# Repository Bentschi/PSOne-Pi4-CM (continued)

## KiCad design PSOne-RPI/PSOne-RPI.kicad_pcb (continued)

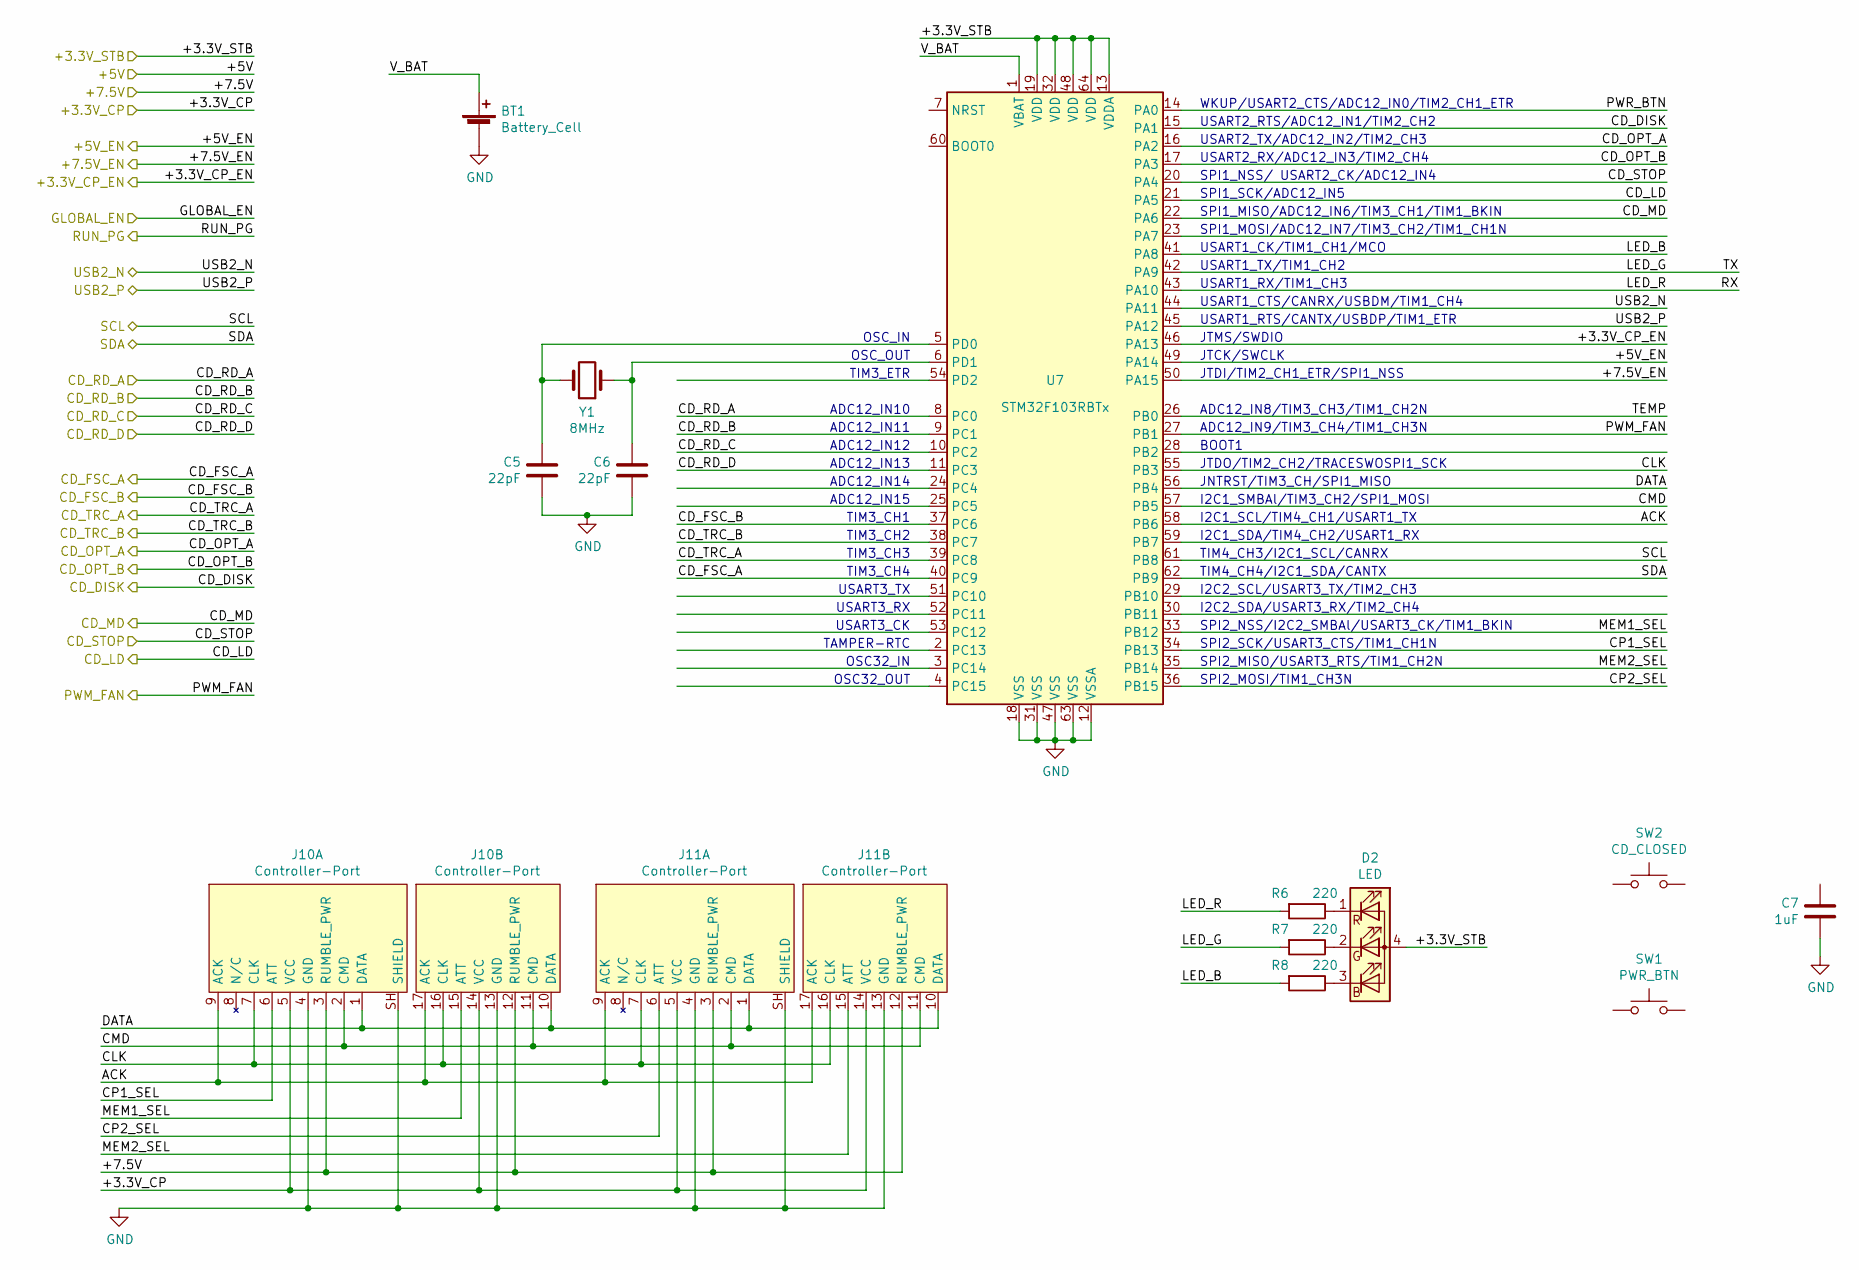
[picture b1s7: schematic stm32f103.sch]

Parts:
BT1: Battery_Cell; BatteryHolder_Keystone_1058_1x2032
C5, C6: 22pF; C_1206_3216Metric
C7: 1uF; C_1206_3216Metric
D2: LED; LED_RGB_1210
J10, J11: Controller-Port; PSOne-Controller-Port
R6, R7, R8: 220; R_1206_3216Metric
SW1: PWR_BTN; SW_Cherry_MX_1.00u_PCB
SW2: CD_CLOSED; SW_PUSH_6mm_H8.5mm
U7: STM32F103RBTx; LQFP-64_10x10mm_P0.5mm
Y1: 8MHz; Crystal_SMD_7050-2Pin_7.0x5.0mm

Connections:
/+3.3V_STB: D2.4 (A), U7.13 (VDDA), U7.19 (VDD), U7.32 (VDD), U7.48 (VDD), U7.64 (VDD); also elsewhere on the board
/+5V_EN: U7.49 (PA14)
/+7.5V: J10.3 (RUMBLE_PWR), J10.12 (RUMBLE_PWR), J11.3 (RUMBLE_PWR), J11.12 (RUMBLE_PWR); also elsewhere on the board
/+7.5V_EN: U7.50 (PA15)
/CD-Interface/+3.3V_CP: J10.5 (VCC), J10.14 (VCC), J11.5 (VCC), J11.14 (VCC); also elsewhere on the board
/CD-Interface/+3.3V_CP_EN: U7.46 (PA13)
/CD-Interface/CD_DISK: U7.15 (PA1); also elsewhere on the board
/CD-Interface/CD_FSC_A: U7.40 (PC9); also elsewhere on the board
/CD-Interface/CD_FSC_B: U7.37 (PC6); also elsewhere on the board
/CD-Interface/CD_LD: U7.21 (PA5); also elsewhere on the board
/CD-Interface/CD_MD: U7.22 (PA6); also elsewhere on the board
/CD-Interface/CD_OPT_A: U7.16 (PA2); also elsewhere on the board
/CD-Interface/CD_OPT_B: U7.17 (PA3); also elsewhere on the board
/CD-Interface/CD_RD_A: U7.8 (PC0); also elsewhere on the board
/CD-Interface/CD_RD_B: U7.9 (PC1); also elsewhere on the board
/CD-Interface/CD_RD_C: U7.10 (PC2); also elsewhere on the board
/CD-Interface/CD_RD_D: U7.11 (PC3); also elsewhere on the board
/CD-Interface/CD_STOP: U7.20 (PA4); also elsewhere on the board
/CD-Interface/CD_TRC_A: U7.39 (PC8); also elsewhere on the board
/CD-Interface/CD_TRC_B: U7.38 (PC7); also elsewhere on the board
/CD-Interface/PWM_FAN: U7.27 (PB1); also elsewhere on the board
/STM32F103/ACK: J10.9 (ACK), J10.17 (ACK), J11.9 (ACK), J11.17 (ACK), U7.58 (PB6)
/STM32F103/CLK: J10.7 (CLK), J10.16 (CLK), J11.7 (CLK), J11.16 (CLK), U7.55 (PB3)
/STM32F103/CMD: J10.2 (CMD), J10.11 (CMD), J11.2 (CMD), J11.11 (CMD), U7.57 (PB5)
/STM32F103/CP1_SEL: J10.6 (ATT), U7.34 (PB13)
/STM32F103/CP2_SEL: J11.6 (ATT), U7.36 (PB15)
/STM32F103/DATA: J10.1 (DATA), J10.10 (DATA), J11.1 (DATA), J11.10 (DATA), U7.56 (PB4)
/STM32F103/LED_B: R8.2, U7.41 (PA8)
/STM32F103/LED_G: R7.2, U7.42 (PA9)
/STM32F103/LED_R: R6.2, U7.43 (PA10)
/STM32F103/MEM1_SEL: J10.15 (ATT), U7.33 (PB12)
/STM32F103/MEM2_SEL: J11.15 (ATT), U7.35 (PB14)
/STM32F103/PWR_BTN: U7.14 (PA0)
/STM32F103/SCL: U7.61 (PB8); also elsewhere on the board
/STM32F103/SDA: U7.62 (PB9); also elsewhere on the board
/STM32F103/TEMP: U7.26 (PB0)
/STM32F103/USB2_N: U7.44 (PA11); also elsewhere on the board
/STM32F103/USB2_P: U7.45 (PA12); also elsewhere on the board
/STM32F103/V_BAT: BT1.1 (+), U7.1 (VBAT)
GND: BT1.2 (-), C5.1, C6.1, C7.1, J10.4 (GND), J10.13 (GND), J10.SH (SHIELD), J11.4 (GND), J11.13 (GND), J11.SH (SHIELD), U7.12 (VSSA), U7.18 (VSS), U7.31 (VSS), U7.47 (VSS), U7.63 (VSS); also elsewhere on the board
unnamed: C5.2, U7.5 (PD0), Y1.2
unnamed: C6.2, U7.6 (PD1), Y1.1
unnamed: D2.1 (RK), R6.1
unnamed: D2.2 (GK), R7.1
unnamed: D2.3 (BK), R8.1

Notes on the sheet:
OSC_IN
OSC_OUT
ADC12_IN10
ADC12_IN11
ADC12_IN12
ADC12_IN13
TAMPER-RTC
OSC32_IN
OSC32_OUT
WKUP/USART2_CTS/ADC12_IN0/TIM2_CH1_ETR
USART2_RTS/ADC12_IN1/TIM2_CH2
USART2_TX/ADC12_IN2/TIM2_CH3
USART2_RX/ADC12_IN3/TIM2_CH4
SPI1_NSS/ USART2_CK/ADC12_IN4
SPI1_SCK/ADC12_IN5
SPI1_MISO/ADC12_IN6/TIM3_CH1/TIM1_BKIN
SPI1_MOSI/ADC12_IN7/TIM3_CH2/TIM1_CH1N
ADC12_IN14
ADC12_IN15
ADC12_IN8/TIM3_CH3/TIM1_CH2N
ADC12_IN9/TIM3_CH4/TIM1_CH3N
I2C2_SDA/USART3_RX/TIM2_CH4
I2C2_SCL/USART3_TX/TIM2_CH3
SPI2_NSS/I2C2_SMBAl/USART3_CK/TIM1_BKIN
SPI2_SCK/USART3_CTS/TIM1_CH1N
SPI2_MISO/USART3_RTS/TIM1_CH2N
SPI2_MOSI/TIM1_CH3N
USART1_CK/TIM1_CH1/MCO
USART1_TX/TIM1_CH2
USART1_RX/TIM1_CH3
USART1_CTS/CANRX/USBDM/TIM1_CH4
USART1_RTS/CANTX/USBDP/TIM1_ETR
JTMS/SWDIO
JTDI/TIM2_CH1_ETR/SPI1_NSS
JTCK/SWCLK
USART3_TX
USART3_RX
USART3_CK
JTDO/TIM2_CH2/TRACESWOSPI1_SCK
JNTRST/TIM3_CH/SPI1_MISO

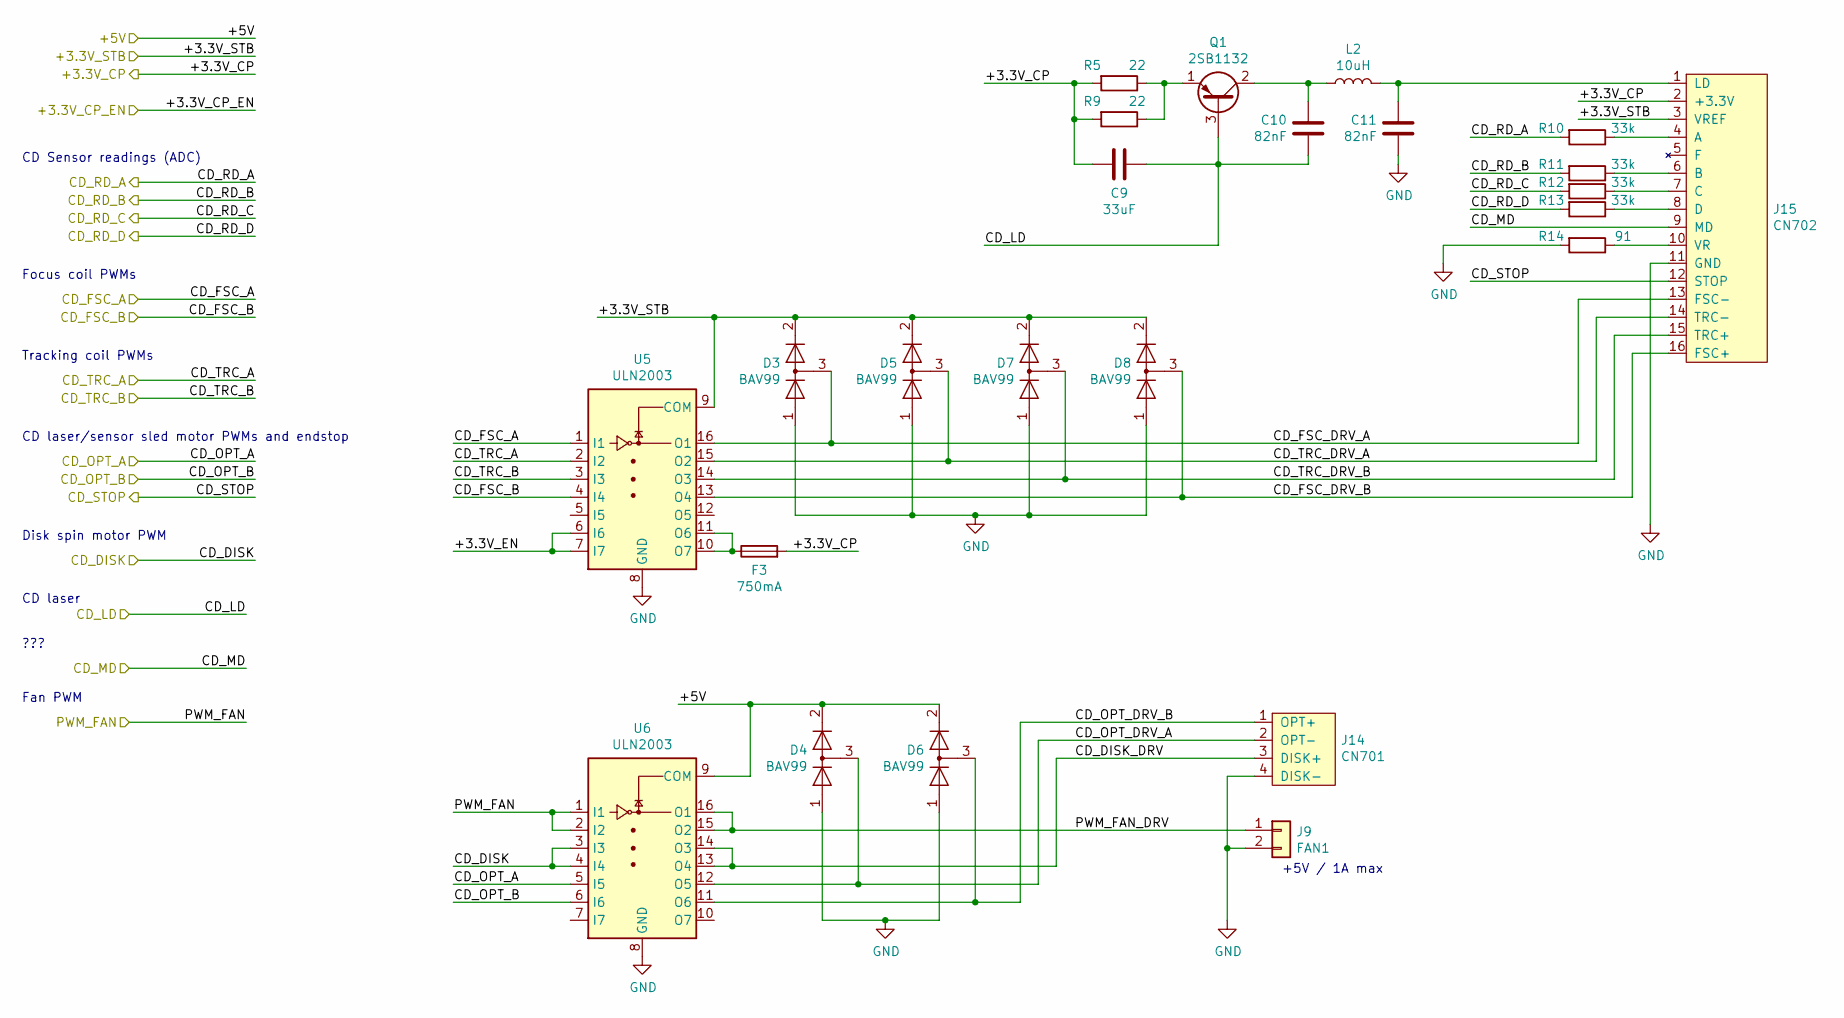
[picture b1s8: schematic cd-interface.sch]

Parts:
C9: 33uF; C_1206_3216Metric
C10, C11: 82nF; C_1206_3216Metric
D3, D4, D5, D6, D7, D8: BAV99; SOT-23
F3: 750mA; Fuse_1210_3225Metric
J9: FAN1; Hirose_DF13-02P-1.25DSA_1x02_P1.25mm_Vertical
J14: CN701; Hirose_DF13-04P-1.25DSA_1x04_P1.25mm_Vertical
J15: CN702; FFC-1x16-Vertical
L2: 10uH; L_1812_4532Metric
Q1: 2SB1132; SOT-23
R5, R9: 22; R_1206_3216Metric
R10, R11, R12, R13: 33k; R_1206_3216Metric
R14: 91; R_1206_3216Metric
U5, U6: ULN2003; SOIC-16_3.9x9.9mm_P1.27mm

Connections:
/+3.3V_STB: D3.2 (A), D5.2 (A), D7.2 (A), D8.2 (A), J15.3 (VREF), U5.9 (COM); also elsewhere on the board
/+5V: D4.2 (A), D6.2 (A), U6.9 (COM)
/CD-Interface/+3.3V_CP: C9.1, F3.2, J15.2 (+3.3V), R5.2, R9.2; also elsewhere on the board
/CD-Interface/+3.3V_EN: U5.6 (I6), U5.7 (I7)
/CD-Interface/CD_DISK: U6.3 (I3), U6.4 (I4); also elsewhere on the board
/CD-Interface/CD_DISK_DRV: J14.3 (DISK+), U6.13 (O4), U6.14 (O3)
/CD-Interface/CD_FSC_A: U5.1 (I1); also elsewhere on the board
/CD-Interface/CD_FSC_B: U5.4 (I4); also elsewhere on the board
/CD-Interface/CD_FSC_DRV_A: D3.3 (K), J15.13 (FSC-), U5.16 (O1)
/CD-Interface/CD_FSC_DRV_B: D8.3 (K), J15.16 (FSC+), U5.13 (O4)
/CD-Interface/CD_LD: C9.2, C10.1, Q1.3 (B); also elsewhere on the board
/CD-Interface/CD_MD: J15.9 (MD); also elsewhere on the board
/CD-Interface/CD_OPT_A: U6.5 (I5); also elsewhere on the board
/CD-Interface/CD_OPT_B: U6.6 (I6); also elsewhere on the board
/CD-Interface/CD_OPT_DRV_A: D4.3 (K), J14.2 (OPT-), U6.12 (O5)
/CD-Interface/CD_OPT_DRV_B: D6.3 (K), J14.1 (OPT+), U6.11 (O6)
/CD-Interface/CD_RD_A: R10.2; also elsewhere on the board
/CD-Interface/CD_RD_B: R11.2; also elsewhere on the board
/CD-Interface/CD_RD_C: R12.2; also elsewhere on the board
/CD-Interface/CD_RD_D: R13.2; also elsewhere on the board
/CD-Interface/CD_STOP: J15.12 (STOP); also elsewhere on the board
/CD-Interface/CD_TRC_A: U5.2 (I2); also elsewhere on the board
/CD-Interface/CD_TRC_B: U5.3 (I3); also elsewhere on the board
/CD-Interface/CD_TRC_DRV_A: D5.3 (K), J15.14 (TRC-), U5.15 (O2)
/CD-Interface/CD_TRC_DRV_B: D7.3 (K), J15.15 (TRC+), U5.14 (O3)
/CD-Interface/PWM_FAN: U6.1 (I1), U6.2 (I2); also elsewhere on the board
/CD-Interface/PWM_FAN_DRV: J9.1, U6.15 (O2), U6.16 (O1)
GND: C11.1, D3.1 (K), D4.1 (K), D5.1 (K), D6.1 (K), D7.1 (K), D8.1 (K), J9.2, J14.4 (DISK-), J15.11 (GND), R14.2, U5.8 (GND), U6.8 (GND); also elsewhere on the board
unnamed: C10.2, L2.1, Q1.2 (C)
unnamed: C11.2, J15.1 (LD), L2.2
unnamed: F3.1, U5.10 (O7), U5.11 (O6)
unnamed: J15.4 (A), R10.1
unnamed: J15.6 (B), R11.1
unnamed: J15.7 (C), R12.1
unnamed: J15.8 (D), R13.1
unnamed: J15.10 (VR), R14.1
unnamed: Q1.1 (E), R5.1, R9.1

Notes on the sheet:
+5V / 1A max
Tracking coil PWMs
Focus coil PWMs
CD Sensor readings (ADC)
CD laser/sensor sled motor PWMs and endstop
Disk spin motor PWM
CD laser
???
Fan PWM

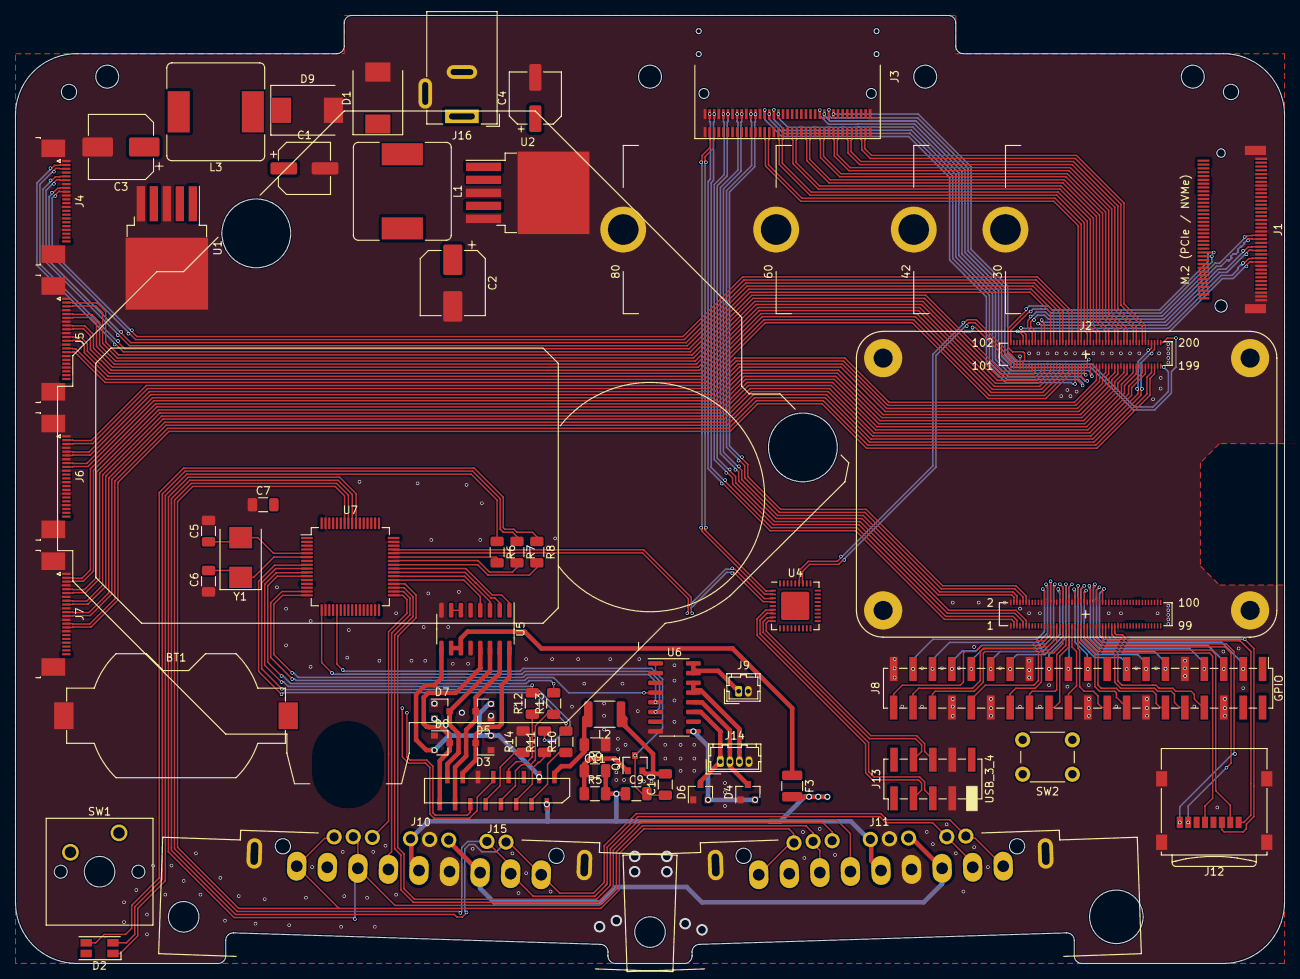
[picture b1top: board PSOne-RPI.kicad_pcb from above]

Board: 2 copper layers, 166.0 x 124.0 mm, 61 parts (0 on the bottom side), 183 nets.

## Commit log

2020-12-28 Added schematic pdf
2020-12-29 Cleaned schematic and moved CD interface to extra sheet
2020-12-29 Fixed naming FAN to PWM_FAN
2020-12-29 Finished CD drive interface circuit
2020-12-29 Updated schematic pdf
2020-12-30 Updated internal power supply
2021-01-01 Corrected estimated power consumption according to schematic step down conversion
2021-01-01 Added possibility to use the STM32 as RTC
